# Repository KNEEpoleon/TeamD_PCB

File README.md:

# TeamD_PCB

This repository contains the PCB design and control system for the BONEPARTE project's drilling subsystem. The project focuses on the development of a printed circuit board (PCB) and associated control mechanisms to support the drilling operations within the BONEPARTE system.

## Files Included:
- **Fusion_Files**: Containsschematic and board design files for the PCB.
- **Gerber_Files**: Contains Gerber files for PCB manufacturing.
- **Libraries**: Custom libraries used in the PCB design.
- **Schematic**: PDF overview the PCB design.
- **BOM**: Bill of Materials for the PCB.
- **DFM**: Design for Manufacturing document outlining manufacturing requirements.

## Installation and Usage
1. Open the Fusion 360 files to modify the PCB design.
2. Use Gerber files for manufacturing the PCB.
3. Refer to the schematic and BOM for assembly and component selection.

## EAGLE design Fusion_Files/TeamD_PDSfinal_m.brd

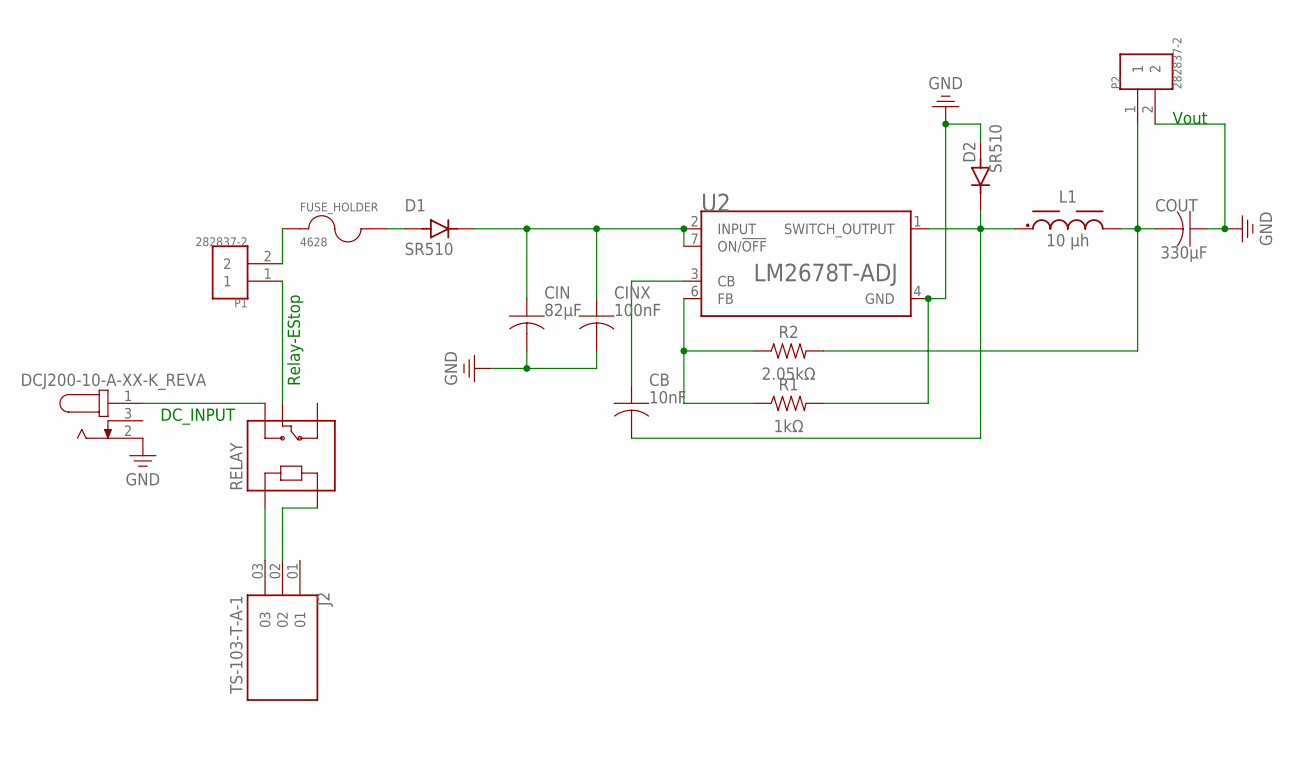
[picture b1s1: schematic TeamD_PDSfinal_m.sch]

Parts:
CB: 10nF; CAPRD550W60D1025H1250B
CIN: 82μF; CAPRD550W60D1025H1250B
CINX: 100nF; CAPRD550W60D1025H1250B
COUT: 330μF; CAPRD550W60D1025H1250B
D1, D2: SR510; DIOAD1990W125L900D530
FUSE_HOLDER: 4628; FUSE_4628
J1: DCJ200-10-A-XX-K_REVA; GCT_DCJ200-10-A-XX-K_REVA
J2: TS-103-T-A-1; SAMTEC_TS-103-T-A-1
L1: 10 µh; WE-TIS_1111
P1, P2: 282837-2; TE_282837-2
R1: 1kΩ; RESAD724W46L381D178B
R2: 2.05kΩ; RESAD724W46L381D178B
RELAY: SRD-05VDC-SL-C; RELAY_SRD-05VDC-SL-C
U2: LM2678T-ADJ; TO127P1041X469X2199-7N

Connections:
ARDUINO: J2.02, RELAY.A2
ARDUINO_2: J2.03, RELAY.A1
D1_LM2678: CIN.1, CINX.1, D1.C (K), U2.2 (INPUT), U2.7 (ON/!OFF)
DC_RELAY: J1.1, RELAY.NO
ESTOP_FUSE: FUSE_HOLDER.1, P1.2
FUSE_DIODE: D1.A, FUSE_HOLDER.2
GND: CIN.2, CINX.2, COUT.1, D2.A, J1.2, P2.2, R1.2, U2.4 (GND)
IC_CB: CB.1, U2.3 (CB)
IC_R: R1.1, R2.1, U2.6 (FB)
L1_OUT: COUT.2, L1.2, P2.1, R2.2
OUTPUT_L1: CB.2, D2.C (K), L1.1, U2.1 (SWITCH_OUTPUT)
RELAY_ESTOP: P1.1, RELAY.COM

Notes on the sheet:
Vout
DC_INPUT
Relay-EStop

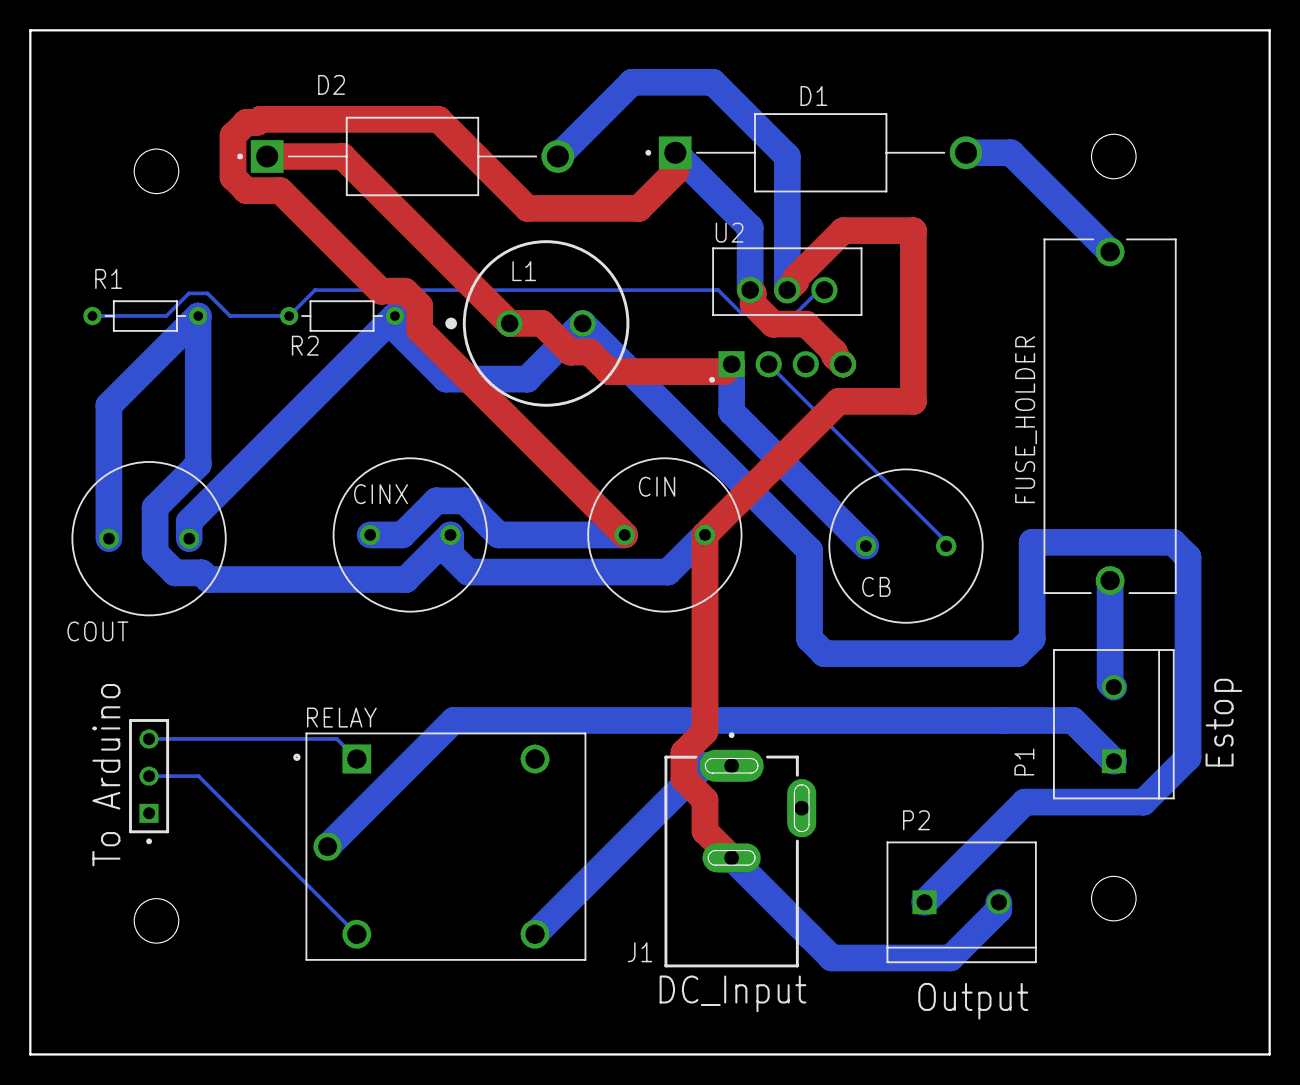
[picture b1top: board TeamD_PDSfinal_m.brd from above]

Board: 2 copper layers, 84.8 x 70.1 mm, 16 parts (0 on the bottom side), 12 nets.

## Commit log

2025-03-19 final commit
